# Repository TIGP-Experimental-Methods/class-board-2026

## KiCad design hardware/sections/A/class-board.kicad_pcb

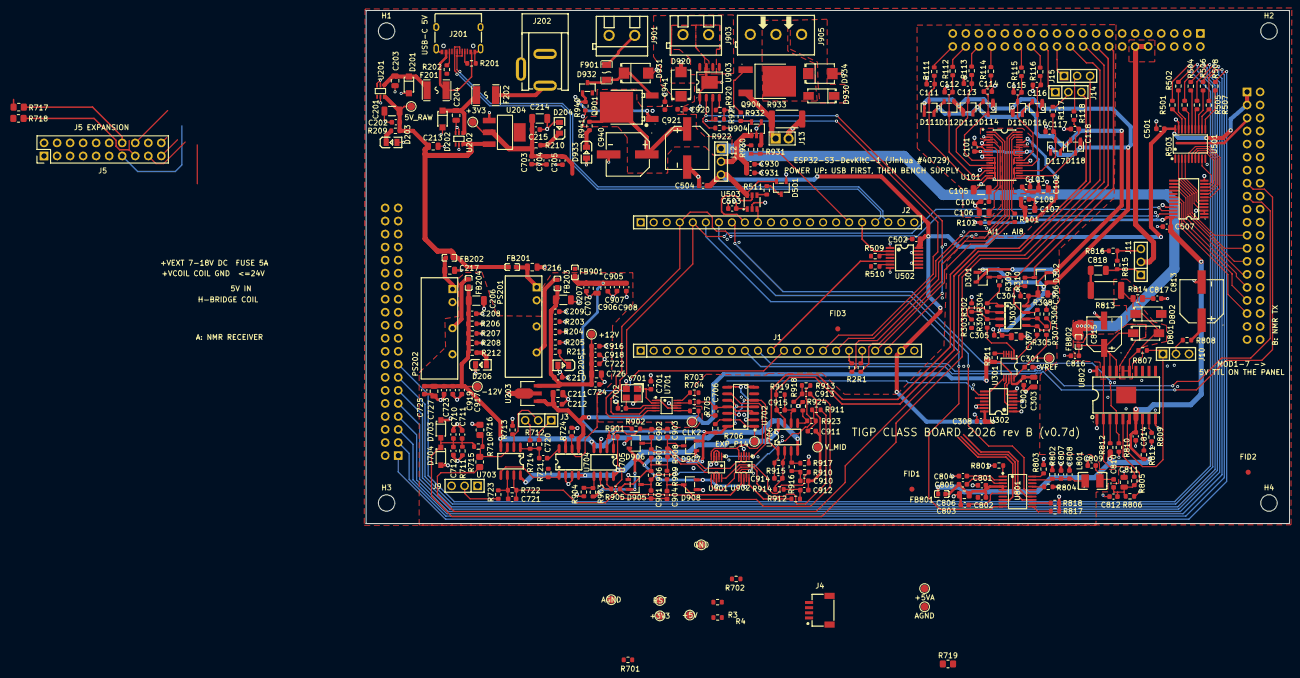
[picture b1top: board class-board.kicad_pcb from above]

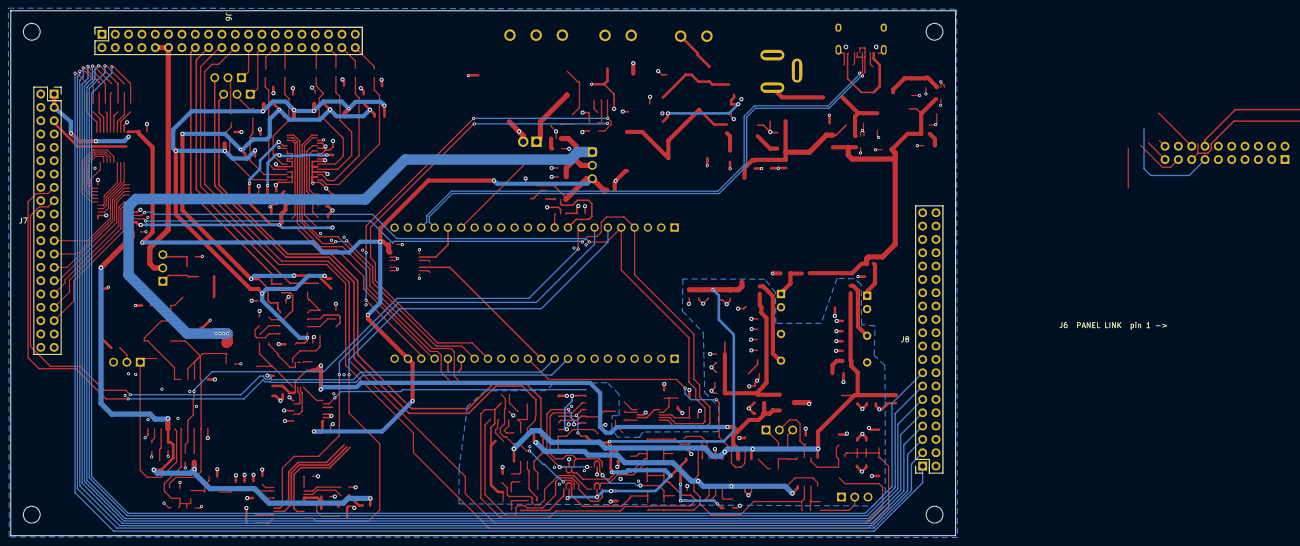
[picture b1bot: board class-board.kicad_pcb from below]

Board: 4 copper layers, 180.0 x 100.0 mm, 334 parts (3 on the bottom side), 216 nets.

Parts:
C101, C103, C104, C210, C301, C704, C810, C930: 1uF; C_0603_1608Metric
C102, C106, C107, C203, C204, C211, C213, C216, C217, C303, C306, C307, C726, C727, C806, C811, C905: 10uF; C_0805_2012Metric
C105, C201, C206, C207, C214: 22uF; C_1206_3216Metric
C108, C202, C208, C209, C212, C215, C302, C304, C305, C308, C501, C502, C503, C504, C507, C703, C705, C707, C722, C723, C724, C725, C801, C802, C803, C812, C814, C816, C906, C907, C908, C916, C917, C918, C919, C920, C931, C941: 100nF; C_0603_1608Metric
C111, C112, C113, C114, C115, C116, C117, C118: 1nF; C_0603_1608Metric
C701, C702: 3.9pF; C_0603_1608Metric
C706: 47pF; C_0603_1608Metric
C710: 1.2nF; C_0603_1608Metric
C711, C721: 100pF; C_0603_1608Metric
C712: 22pF; C_0603_1608Metric
C720, C804, C805, C817, C901, C902, C903, C904, C910, C911, C912, C913: 10nF; C_0603_1608Metric
C807: 20pF; C_0603_1608Metric
C808: 390pF; C_0603_1608Metric
C809: 130pF; C_0603_1608Metric
C813, C921, C940: 100uF 35V; CAP-SMD_BD8.0-L8.3-W8.3-LS9.3-FD
C815: 47uF 35V; CAP-SMD_BD6.3-L6.6-W6.6-FD
C818: 10uF; C_1206_3216Metric
C914, C915: 560pF; C_0603_1608Metric
D111, D112, D113, D114, D115, D116, D117, D118, D301, D302, D501, D905, D906, D907, D908: BAV99; SOT-23-3_L2.9-W1.6-P1.90-LS2.8-BR
D201, D202: SMF5.0A; SOD-123FL_L2.7-W1.8-LS3.8-RD
D203, D204, D205, D206, D933: GREEN; LED0805-R-RD
D703, D704: 1N4148W; SOD-123F_L2.7-W1.6-LS3.8-RD
D801, D802, D930: SS54; SMA_L4.4-W2.8-LS5.4-R-RD
D920, D931: SMBJ26A; SMB_L4.6-W3.6-LS5.3-RD
D932: BZX84C12; SOT-23-3_L2.9-W1.3-P1.90-LS2.4-BR
D934: SMBJ20A; SMB_L4.6-W3.6-LS5.3-RD
F201, F202: 1.5A polyfuse; F1812
F901: 5A fast; F1206
FB201, FB202, FB203, FB204, FB801, FB901: 600R@100MHz; L0603
FB802: 120R@100MHz 3A; L0603
FID1, FID2, FID3: Fiducial; Fiducial_1mm_Mask2mm
H1, H2, H3, H4: M3; MountingHole_3.2mm_M3
J1: DevKit J1 (left row); HDR-TH_22P-P2.54-V-F
J2: DevKit J3 (right row); HDR-TH_22P-P2.54-V-F
J3, J9, J10, J11, J12, J14, J15: C2937625_-_Conn_01x03; C2937625-HDR-TH_3P-P2.54-V-M
J4: Qwiic; CONN-SMD_4P-P1.00_XY-SM04B-SRSS-TB
J5: Expansion 2x10; PinHeader_2x10_P2.54mm_Vertical
J6, J7, J8: Panel link 2x20 female; PinSocket_2x20_P2.54mm_Vertical
J13: C492401-PZ254V-11-02P; C492401-HDR-TH_2P-P2.54-V-M
J201: USB-C 16P; USB-C-SMD_TYPE-C-16PIN-2MD-073
J202: DC005-T20; DC-IN-TH_DC005-T20
J901, J903: KF301-5.0-2P; CONN-TH_P5.00_KF301-5.0-2P
J905: KF301-5.0-3P; CONN-TH_3P-P5.00_KF301-5.0-3P
L801: 15uH; IND-SMD_L3.2-W2.5-LQH32CN1R0M53L
PS201, PS202: B0512S-2WR3; PWRM-TH_IBXX05S-2WR3
Q901: AOD4185; TO-252-3_L6.6-W6.1-P4.57-LS9.9-BR-CW
Q904: AOD4184A; TO-252-2_L6.6-W6.1-P4.57-LS9.9-TL-CW
R1, R2, R101, R511, R703, R705: 33; R_0603_1608Metric
R3, R4, R211, R212, R701, R702, R941: 4.7k; R_0603_1608Metric
R102, R301, R303, R305, R307, R311, R706, R721, R724, R804, R810, R811, R812, R817, R818, R903, R904, R906, R907, R908, R909, R921, R922, R930: 10k; R_0603_1608Metric
R111, R112, R113, R114, R115, R116, R117, R118, R209, R210, R501, R502, R503, R504, R505, R506, R507, R508: 1k; R_0603_1608Metric
R201, R202: 5.1k; R_0603_1608Metric
R203, R204, R205, R206, R207, R208: 2.2k; R_0603_1608Metric
R302, R304, R306, R308: 40.2k; R_0603_1608Metric
R309, R310, R509, R510: 49.9; R_0603_1608Metric
R704, R710, R713, R816, R905, R931: 100; R_0603_1608Metric
R711: 1M; R_0603_1608Metric
R712, R901, R902: 10.0k; R_0603_1608Metric
R714, R723, R910, R911, R912, R913, R914, R916, R918, R923: 1.00k; R_0603_1608Metric
R715, R716: 0R; R_0805_2012Metric_Pad1.20x1.40mm_HandSolder
R717, R718, R719: 0; R_0805_2012Metric_Pad1.20x1.40mm_HandSolder
R722: 9.1k; R_0603_1608Metric
R801: 6.8k; R_0603_1608Metric
R802, R803: 200; R_0603_1608Metric
R805, R806: 100k; R_0603_1608Metric
R807: 6.49k; R_0603_1608Metric
R808: 270; R_0603_1608Metric
R809: 11k; R_0603_1608Metric
R813: 4.7 1W; R_2512_6332Metric
R814: 10; R_0805_2012Metric
R815: 910; R_0603_1608Metric
R915, R917, R919, R924: 20.0k; R_0603_1608Metric
R920: 32k; R_0603_1608Metric
R932: 10; R_0603_1608Metric
R933: 0R; R_2512_6332Metric
R940: 47k; R_0603_1608Metric
TP1: RST; TestPoint_Pad_D1.5mm
TP2: GND; TestPoint_Pad_D1.5mm
TP3, TP202: +3V3; TestPoint_Pad_D1.5mm
TP4: +5V; TestPoint_Pad_D1.5mm
TP101, TP206: AGND; TestPoint_Pad_D1.5mm
TP201: 5V_RAW; TestPoint_Pad_D1.5mm
TP203: +12V; TestPoint_Pad_D1.5mm
TP204: -12V; TestPoint_Pad_D1.5mm
TP205: +5VA; TestPoint_Pad_D1.5mm
TP301: VREF; TestPoint_Pad_D1.5mm
TP501: EXP_P14; TestPoint_Pad_D1.5mm
TP701: CLK2; TestPoint_Pad_D1.5mm
TP702: V_MID; TestPoint_Pad_D1.5mm
U101: ADS8688IDBTR; TSSOP-38_L9.7-W4.4-P0.50-LS6.4-BL
U201, U202: LM66100DCKR; SC-70-6_L2.0-W1.3-P0.65-LS2.1-BL
U203: 78L05G-AB3-R; SOT-89-3_L4.5-W2.5-P1.50-LS4.2-BR
U204: AMS1117-3.3; SOT-223-3_L6.5-W3.4-P2.30-LS7.0-BR
U301: DAC8563SDGSR; VSSOP-10_L3.0-W3.0-P0.50-LS4.9-BL
U302, U502: 74HCT125PW; TSSOP-14_L5.0-W4.4-P0.65-LS6.4-BL
U303: OPA2192IDR; SOIC-8_L4.9-W3.9-P1.27-LS6.0-BL
U501: SN74AHCT541PWR; TSSOP-20_L6.5-W4.4-P0.65-LS6.4-BL
U503: SN74LVC1T45DBVR; SOT-23-6_L2.9-W1.6-P0.95-LS2.8-BR
U505: TCA9535PWR; TSSOP-24_L7.8-W4.4-P0.65-LS6.4-BL
U701: SI5351A-B-GT; MSOP-10_L3.0-W3.0-P0.50-LS5.0-BL
U702: 74HC74D,653; SOIC-14_L8.7-W3.9-P1.27-LS6.0-BL
U703: OPA1656IDR; SOIC-8_L5.0-W4.0-P1.27-LS6.0-BL
U704: DG419DY-T1-E3; SOIC-8_L4.9-W3.9-P1.27-LS6.0-BL
U705, U706: OPA1612AIDR; SOIC-8_L5.0-W4.0-P1.27-LS6.0-BL
U801: AD9834BRUZ; TSSOP-20_L6.5-W4.4-P0.65-LS6.4-BL
U802: OPA564AIDWPR; HSOP-20_L12.9-W7.5-P1.27-BL-EP-A
U901, U902: TS5A23157DGSR; MSOP-10_L3.0-W3.0-P0.50-LS5.0-BL
U903: DRV8871DDAR; SO-8_L4.9-W3.9-P1.27-LS6.0-BL-EP
U904: UCC27517DBVR; SOT-23-5_L3.0-W1.7-P0.95-LS2.8-BR
Y701: 25 MHz; CRYSTAL-SMD_4P-L3.2-W2.5-BL

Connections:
+3V3: C107.1, C108.1, C214.1, C215.1, C503.1, C507.1, C703.1, C704.1, C705.1, C814.1, FB801.1, FB901.1, J4.2 (3V3), J5.1, J7.5, J8.27, J8.29, R3.1, R4.1, R102.1, R210.1, R701.1, R702.1, R811.1, R812.1, TP3.1 (1_1), TP202.1 (1_1), U101.34 (DVDD), U204.2 (VOUT), U503.1 (VCCA), U505.24 (VCC), U701.1 (VDD), U701.7 (VDDO), U802.7 (VDIG)
+3V3A: C707.1, C905.1, C906.1, C907.1, C908.1, D905.2 (K2), D906.2 (K2), D907.2 (K2), D908.2 (K2), FB901.2, R706.1, R903.1, U702.4 (~1PRE), U702.10 (~2PRE), U702.14 (VCC), U901.8 (V+), U902.8 (V+)
+5VA: C101.1, C102.1, C103.1, C211.1, C212.1, C302.1, C303.1, R311.2, TP205.1 (1_1), U101.9 (AVDD), U101.30 (AVDD), U203.1 (OUT), U301.9 (AVDD), U704.5 (VL)
+5V_RAW: C201.1, C202.1, C213.1, C308.1, C501.1, C502.1, C504.1, D501.2 (K2), FB201.1, FB202.1, J1.21 (5V), J5.2, J7.1, J7.3, J12.3, R209.1, TP4.1 (1_1), TP201.1 (1_1), U201.6 (VOUT), U202.6 (VOUT), U204.3 (VIN), U302.14 (VCC), U501.20 (VCC), U502.14 (VCC), U503.6 (VCCB)
+12V: C207.1, C209.1, C210.1, C304.1, C306.1, C722.1, C724.1, C726.1, C916.1, C918.1, D111.2 (K2), D112.2 (K2), D113.2 (K2), D114.2 (K2), D115.2 (K2), D116.2 (K2), D117.2 (K2), D118.2 (K2), D301.2 (K2), D302.2 (K2), FB203.2, J5.3, R203.1, R204.1, R205.1, R211.1, TP203.1 (1_1), U203.3 (IN), U303.8 (V+), U703.8 (V+), U704.4 (V+), U705.8 (V+), U706.8 (V+)
+VCOIL: D930.2 (K), J905.1
+VEXT: C920.1, C921.1, C940.1, C941.1, D920.1 (K), FB802.1, J12.1, Q901.2 (D), R941.1, U903.5 (VM)
-12V: C206.1, C208.1, C305.1, C307.1, C723.1, C725.1, C727.1, C917.1, C919.1, D111.1 (A1), D112.1 (A1), D113.1 (A1), D114.1 (A1), D115.1 (A1), D116.1 (A1), D117.1 (A1), D118.1 (A1), D301.1 (A1), D302.1 (A1), FB204.2, J5.4, R206.1, R207.1, R208.1, R212.1, TP204.1 (1_1), U303.4 (V-), U703.4 (V-), U704.7 (V-), U705.4 (V-), U706.4 (V-)
/b1_inputs/ADC_RST: R102.2, U101.2 (~RST/~PD)
/b1_inputs/AI1: J6.40, R111.1
/b1_inputs/AI2: J6.38, R112.1
/b1_inputs/AI3: J6.36, R113.1
/b1_inputs/AI4: J6.34, R114.1
/b1_inputs/AI5: J6.30, R115.1
/b1_inputs/AI6: J6.28, R116.1
/b1_inputs/AI7: J6.26, J14.1
/b1_inputs/AI8: J6.24, J15.1
/b1_inputs/AIN1: C111.1, D111.3 (COM), R111.2, U101.18 (AIN_1P)
/b1_inputs/AIN2: C112.1, D112.3 (COM), R112.2, U101.16 (AIN_0P)
/b1_inputs/AIN3: C113.1, D113.3 (COM), R113.2, U101.14 (AIN_7P)
/b1_inputs/AIN4: C114.1, D114.3 (COM), R114.2, U101.12 (AIN_6P)
/b1_inputs/AIN5: C115.1, D115.3 (COM), R115.2, U101.27 (AIN_5P)
/b1_inputs/AIN6: C116.1, D116.3 (COM), R116.2, U101.25 (AIN_4P)
/b1_inputs/AIN7: C117.1, D117.3 (COM), R117.2, U101.23 (AIN_3P)
/b1_inputs/AIN8: C118.1, D118.3 (COM), R118.2, U101.21 (AIN_2P)
/b1_inputs/AO1: D301.3 (COM), J6.18, R309.2
/b1_inputs/AO2: D302.3 (COM), J6.16, R310.2
/b1_inputs/AUX: C710.2, C711.2, C712.2, D703.2 (A), D704.1 (K), J6.20, R710.2, R711.2
/b1_inputs/COND_OUT1: C914.2, J14.3, R915.2, U706.1
/b1_inputs/COND_OUT2: C915.2, J15.3, R919.2, U706.7
/b1_inputs/CS_ADC: J1.16 (IO10), U101.38 (~CS)
/b1_inputs/RX: J6.22, R715.2
/b1_inputs/TX: J6.10, J6.12, J11.2
/b2_power/USB_D_N: J2.20 (IO19), J201.A7 (D-), J201.B7 (D-)
/b2_power/USB_D_P: J2.19 (IO20), J201.A6 (D+), J201.B6 (D+)
/b3_outputs/CS_DAC: J1.5 (IO5), U302.9 (3A)
/b3_outputs/DAC_A: R301.1, U301.1 (VOUTA)
/b3_outputs/DAC_B: R305.1, U301.2 (VOUTB)
/b3_outputs/DAC_DIN: U301.8 (DIN), U302.6 (2Y)
/b3_outputs/DAC_SCLK: U301.7 (SCLK), U302.3 (1Y)
/b3_outputs/DAC_SYNC: U301.6 (~SYNC), U302.8 (3Y)
/b3_outputs/VREF_DAC: C301.1, R303.1, R307.1, TP301.1 (1_1), U301.10 (VREFIN/VREFOUT)
/b5_dio_trig/DIO1: U501.2 (A1), U505.4 (P00)
/b5_dio_trig/DIO2: U501.3 (A2), U505.5 (P01)
/b5_dio_trig/DIO3: U501.4 (A3), U505.6 (P02)
/b5_dio_trig/DIO4: U501.5 (A4), U505.7 (P03)
/b5_dio_trig/DIO5: U501.6 (A5), U505.8 (P04)
/b5_dio_trig/DIO6: U501.7 (A6), U505.9 (P05)
/b5_dio_trig/DIO7: U501.8 (A7), U505.10 (P06)
/b5_dio_trig/DIO8: U501.9 (A8), U505.11 (P07)
/b5_dio_trig/EXP_P14: R706.2, TP501.1 (1_1), U505.17 (P14), U702.1 (~1CLR), U702.13 (~2CLR)
/b5_dio_trig/FASTTTL1: J8.39, R509.2
/b5_dio_trig/FASTTTL2: J8.37, R510.2
/b5_dio_trig/FAST_OUT1: J2.18 (IO21), U502.2 (1A)
/b5_dio_trig/FAST_OUT2: J1.11 (IO18), U502.5 (2A)
/b5_dio_trig/LED_ACT: J8.23, R718.2
/b5_dio_trig/LED_WIFI: J8.25, R717.2
/b5_dio_trig/MOD1: J7.23, U505.13 (P10)
/b5_dio_trig/MOD2: J7.25, U505.14 (P11)
/b5_dio_trig/MOD3: J7.27, U505.15 (P12)
/b5_dio_trig/MOD4: J7.29, U505.16 (P13)
/b5_dio_trig/MOD5: J7.31, U505.18 (P15)
/b5_dio_trig/MOD6: J7.33, U505.19 (P16)
/b5_dio_trig/MOD7: J7.35, U505.20 (P17)
/b5_dio_trig/OPTO_IN1: J1.9 (IO16), J7.15
/b5_dio_trig/OPTO_IN2: J1.10 (IO17), J7.17
/b5_dio_trig/TRIG_5V: D501.3 (COM), J8.35, R511.2
/b5_dio_trig/TRIG_DIR: J2.9 (IO39), U503.5 (DIR)
/b5_dio_trig/TTL1: J8.15, R501.2
/b5_dio_trig/TTL2: J8.13, R502.2
/b5_dio_trig/TTL3: J8.11, R503.2
/b5_dio_trig/TTL4: J8.9, R504.2
/b5_dio_trig/TTL5: J8.7, R505.2
/b5_dio_trig/TTL6: J8.5, R506.2
/b5_dio_trig/TTL7: J8.3, R507.2
/b5_dio_trig/TTL8: J8.1, R508.2
/base_mcu/DDS_FSYNC: J2.7 (IO41), U801.15 (~FSYNC)
/base_mcu/DDS_PSEL: J2.6 (IO42), U801.10 (PSELECT)
/base_mcu/FET_GATE: J2.17 (IO47), R930.1, R931.1
/base_mcu/GPIO4: J1.4 (IO4), J5.16
/base_mcu/GPIO6: J1.6 (IO6), J5.17
/base_mcu/GPIO7: J1.7 (IO7), J5.19
/base_mcu/GPIO15: J1.8 (IO15), J5.20
/base_mcu/GPIO43: J2.2 (IO43/TX), J5.14, R717.1
/base_mcu/GPIO44: J2.3 (IO44/RX), J5.15, R718.1
/base_mcu/HB_IN1: J1.15 (IO9), R921.1, U903.3 (IN1)
/base_mcu/HB_IN2: J1.20 (IO14), R922.1, U903.2 (IN2)
/base_mcu/MOSI_MCU: J1.17 (IO11), R2.1
/base_mcu/RST: J1.3 (RST), TP1.1 (1_1)
/base_mcu/RX_BLANK: J1.12 (IO8), R724.1, U704.6 (IN)
/base_mcu/SCLK_MCU: J1.18 (IO12), R1.1
/base_mcu/TRIG_IO: J2.10 (IO38), J5.13, U503.3 (A)
/base_mcu/TX_EN: J2.8 (IO40), R810.1, U802.4 (E/~S)
/c_switch/COIL: D930.1 (A), D934.1 (K), J905.2, Q904.2 (D)
/c_switch/HB_OUT1: J903.1, U903.6 (OUT1)
/c_switch/HB_OUT2: J903.2, U903.8 (OUT2)
/c_switch/ILIM: R920.1, U903.4 (ILIM)
/c_switch/ISENSE_COIL: J13.1, Q904.3 (S), R933.1
/c_switch/VDD904: C930.1, C931.1, J12.2, U904.1 (VDD)
/c_switch/VIN: F901.1, J901.1
/c_switch/VIN_F: D931.1 (K), D932.3 (K), F901.2, Q901.3 (S)
/nmr_rx/BLK_IN: C720.2, U704.8 (S2)
/nmr_rx/CLK0_MCLK: R703.2, U801.8 (MCLK)
/nmr_rx/CLK1: C706.1, R704.2, U702.3 (1CLK), U702.11 (2CLK)
/nmr_rx/DIF_I_N: C914.1, R914.2, R915.1, U706.2 (-)
/nmr_rx/DIF_I_P: R916.2, R917.1, U706.3 (+)
/nmr_rx/DIF_Q_N: C915.1, R918.2, R919.1, U706.6 (-)
/nmr_rx/DIF_Q_P: R923.1, R924.1, U706.5 (+)
/nmr_rx/IF_IN: R912.1, U902.10 (COM1)
/nmr_rx/IF_INF: C912.1, R912.2, R914.1
/nmr_rx/IF_IP: R910.1, U901.10 (COM1)
/nmr_rx/IF_IPF: C910.2, R910.2, R916.1
/nmr_rx/IF_QN: R913.1, U902.6 (COM2)
/nmr_rx/IF_QNF: C913.1, R913.2, R918.1
/nmr_rx/IF_QP: R911.1, U901.6 (COM2)
/nmr_rx/IF_QPF: C911.2, R911.2, R923.2
/nmr_rx/INV_N: R901.2, R902.1, U705.2 (-)
/nmr_rx/LNA1_OUT: C720.1, R712.1, R714.1, U703.1
/nmr_rx/LNA_FB1: J3.2, R713.1, U703.2 (-)
/nmr_rx/LNA_FB2: C721.1, R722.1, R723.1, U703.6 (-)
/nmr_rx/LNA_OUT: C721.2, C901.1, C904.1, R722.2, R901.1, U703.7
/nmr_rx/LO_I: U702.5 (1Q), U702.12 (2D), U901.1 (IN1), U902.1 (IN1)
/nmr_rx/LO_Q: U702.9 (2Q), U901.5 (IN2), U902.5 (IN2)
/nmr_rx/LO_QN: U702.2 (1D), U702.8 (~2Q)
/nmr_rx/RX_IN: R710.1, R715.1, R716.2, U703.3 (+)
/nmr_rx/SN_A: C902.2, D906.3 (COM), R907.1, U901.7 (NC2), U901.9 (NC1)
/nmr_rx/SN_B: C903.2, D907.3 (COM), R908.1, U902.2 (NO1), U902.4 (NO2)
/nmr_rx/SP_A: C901.2, D905.3 (COM), R906.1, U901.2 (NO1), U901.4 (NO2)
/nmr_rx/SP_B: C904.2, D908.3 (COM), R909.1, U902.7 (NC2), U902.9 (NC1)
/nmr_rx/ST2_GAIN: J9.2, R723.2
/nmr_rx/ST2_IN: R721.1, U703.5 (+), U704.1 (D)
/nmr_rx/S_MINUS: C902.1, C903.1, R902.2, U705.1
/nmr_rx/VMID_BUF: R905.1, U705.6 (-), U705.7
/nmr_rx/VMID_DIV: R903.2, R904.1, U705.5 (+)
/nmr_rx/XTAL_A: C701.1, U701.2 (XA), Y701.1 (OSC1)
/nmr_rx/XTAL_B: C702.1, U701.3 (XB), Y701.3 (OSC2)
/nmr_tx/+3V3D: C801.1, C802.1, C805.2, C806.1, FB801.2, U801.4 (AVDD), U801.5 (DVDD)
/nmr_tx/+VEXT_TX: C815.1, C816.1, D801.2 (K), FB802.2, R805.1, U802.2 (V+), U802.17 (V+PWR), U802.18 (V+PWR), U802.19 (V+PWR)
/nmr_tx/DDS_RESET: R817.1, U801.11 (RESET)
/nmr_tx/DDS_SLEEP: R818.1, U801.12 (SLEEP)
/nmr_tx/TX_A: D801.1 (A), D802.2 (K), R807.2, R813.1, R814.1, U802.15 (VOUT), U802.16 (VOUT)
/nmr_tx/TX_FB: J10.1, R807.1, U802.6 (-IN)
/nmr_tx/TX_IFLAG: R811.2, U802.8 (IFLAG)
/nmr_tx/TX_TFLAG: R812.2, U802.3 (TFLAG)
/nmr_tx/TX_VMID: C810.2, C811.1, C812.1, R805.2, R806.1, U802.5 (+IN)
AGND: C101.2, C102.2, C103.2, C104.2, C105.2, C106.2, C111.2, C112.2, C113.2, C114.2, C115.2, C116.2, C117.2, C118.2, C206.2, C207.2, C208.2, C209.2, C210.2, C211.2, C212.2, C301.2, C302.2, C303.2, C304.2, C305.2, C306.2, C307.2, C706.2, C707.2, C710.1, C711.1, C712.1, C722.2, C723.2, C724.2, C725.2, C726.2, C727.2, C801.2, C802.2, C803.2, C804.2, C806.2, C807.2, C808.2, C809.2, C905.2, C906.2, C907.2, C908.2, C916.2, C917.2, C918.2, C919.2, D205.1 (K), D206.2 (A), D703.1 (K), D704.2 (A), D905.1 (A1), D906.1 (A1), D907.1 (A1), D908.1 (A1), J5.18, J6.15, J6.17, J6.19, J6.21, J6.23, J6.25, J6.27, J6.29, J6.31, J6.33, J6.35, J6.37, J6.39, J9.1, PS201.4 (-VO), PS202.6 (+VO), R203.2, R204.2, R205.2, R206.2, R207.2, R208.2, R302.1, R306.1, R711.1, R713.2, R716.1, R719.1, R721.2, R724.2, R801.2, R802.2, R803.2, R804.2, R817.2, R818.2, R904.2, R917.2, R924.2, TP101.1 (1_1), TP206.1 (1_1), U101.4 (~REFSEL), U101.6 (REFGND), U101.8 (AGND), U101.10 (AUX_IN), U101.11 (AUX_GND), U101.13 (AIN_6GND), U101.15 (AIN_7GND), U101.17 (AIN_0GND), U101.19 (AIN_1GND), U101.20 (AIN_2GND), U101.22 (AIN_3GND), U101.24 (AIN_4GND), U101.26 (AIN_5GND), U101.28 (AGND), U101.29 (AGND), U101.31 (AGND), U101.32 (AGND), U203.2 (GND), U301.3 (GND), U301.4 (~LDAC), U702.7 (GND), U704.2 (S1), U704.3 (GND), U705.3 (+), U801.7 (DGND), U801.9 (FSELECT), U801.18 (AGND), U901.3 (GND), U902.3 (GND)
GND: C107.2, C108.2, C201.2, C202.2, C203.2, C204.2, C213.2, C214.2, C215.2, C216.2, C217.2, C308.2, C501.2, C502.2, C503.2, C504.2, C507.2, C701.2, C702.2, C703.2, C704.2, C705.2, C811.2, C812.2, C813.2, C814.2, C815.2, C816.2, C817.2, C920.2, C921.2, C930.2, C931.2, C940.2, C941.2, D201.2 (A), D202.2 (A), D203.1 (K), D204.1 (K), D501.1 (A1), D802.1 (A), D920.2 (A), D931.2 (A), D933.1 (K), D934.2 (A), J1.22 (GND), J2.1 (GND), J2.21 (GND), J2.22 (GND), J4.1 (GND), J4.5 (SHELL), J4.6 (SHELL), J5.5, J5.6, J5.10, J6.1, J6.3, J6.5, J6.7, J6.9, J6.11, J7.2, J7.4, J7.6, J7.8, J7.10, J7.12, J7.14, J7.16, J7.18, J7.20, J7.22, J7.24, J7.26, J7.28, J7.30, J7.32, J7.34, J7.36, J7.38, J7.40, J8.2, J8.4, J8.6, J8.8, J8.10, J8.12, J8.14, J8.16, J8.18, J8.20, J8.22, J8.24, J8.26, J8.28, J8.30, J8.32, J8.34, J8.36, J8.38, J8.40, J13.2, J201.13 (SHIELD), J201.14 (SHIELD), J201.A1B12 (GND), J201.B1A12 (GND), J202.2 (SLEEVE), J901.2, J905.3, PS201.2 (-VIN), PS202.2 (-VIN), R201.2, R202.2, R719.2, R806.2, R809.2, R810.2, R816.2, R920.2, R921.2, R922.2, R930.2, R933.2, R940.2, TP2.1 (1_1), U101.3 (DAISY), U101.33 (DGND), U201.2 (GND), U201.3 (~CE), U201.5 (~ST), U202.2 (GND), U202.3 (~CE), U202.5 (~ST), U204.1 (GND), U302.1 (~1OE), U302.4 (~2OE), U302.7 (GND), U302.10 (~3OE), U302.12 (4A), U302.13 (~4OE), U501.1 (~OE1), U501.10 (GND), U501.19 (~OE2), U502.1 (~1OE), U502.4 (~2OE), U502.7 (GND), U502.9 (3A), U502.10 (~3OE), U502.12 (4A), U502.13 (~4OE), U503.2 (GND), U505.2 (A1), U505.3 (A2), U505.12 (GND), U505.21 (A0), U701.8 (GND), U802.1 (V-), U802.10 (V-), U802.11 (V-), U802.13 (V-PWR), U802.14 (V-PWR), U802.20 (V-), U802.21 (EP), U903.1 (GND), U903.7 (PGND), U903.9 (EP), U904.2 (GND), U904.4 (IN-), Y701.2 (GND), Y701.4 (GND)
I2C_SCL: J2.5 (IO2), J4.4 (SCL), J5.12, J8.31, R4.2, R702.2, U505.22 (SCL), U701.4 (SCL)
I2C_SDA: J2.4 (IO1), J4.3 (SDA), J5.11, J8.33, R3.2, R701.2, U505.23 (SDA), U701.5 (SDA)
unnamed: C809.1, C810.1, L801.2
unnamed: C813.1, R808.2
unnamed: C817.1, R814.2
unnamed: C818.1, R813.2
unnamed: C203.1, D201.1 (K), F201.2, U201.1 (VIN)
unnamed: C204.1, D202.1 (K), F202.2, U202.1 (VIN)
unnamed: D203.2 (A), R209.2
unnamed: D204.2 (A), R210.2
unnamed: D205.2 (A), R211.2
unnamed: D206.1 (K), R212.2
unnamed: D932.1 (A), Q901.1 (G), R940.1
unnamed: D933.2 (A), R941.2
unnamed: F201.1, J201.A4B9 (VBUS), J201.B4A9 (VBUS)
unnamed: J3.1, R712.2
unnamed: J3.3, R714.2
unnamed: J10.2, R808.1
unnamed: C818.2, J11.1, R815.1
unnamed: J11.3, R815.2, R816.1
unnamed: J14.2, R117.1
unnamed: J15.2, R118.1
unnamed: J201.A5 (CC1), R201.1
unnamed: J201.B5 (CC2), R202.1
unnamed: F202.1, J202.1 (TIP)
unnamed: C216.1, FB201.2, PS201.1 (+VIN)
unnamed: FB203.1, PS201.6 (+VO)
unnamed: C217.1, FB202.2, PS202.1 (+VIN)
unnamed: FB204.1, PS202.4 (-VO)
unnamed: Q904.1 (G), R932.2
unnamed: R304.2, R309.1, U303.1
unnamed: R308.2, R310.1, U303.7
unnamed: R705.2, TP701.1 (1_1)
unnamed: C104.1, C105.1, U101.7 (REFCAP)
unnamed: C106.1, U101.5 (REFIO)
unnamed: R101.1, U101.36 (SDO)
unnamed: R311.1, U301.5 (~CLR)
unnamed: R301.2, R302.2, U303.3 (+)
unnamed: R303.2, R304.1, U303.2 (-)
unnamed: R305.2, R306.2, U303.5 (+)
unnamed: R307.2, R308.1, U303.6 (-)
unnamed: R501.1, U501.18 (Y1)
unnamed: R502.1, U501.17 (Y2)
unnamed: R503.1, U501.16 (Y3)
unnamed: R504.1, U501.15 (Y4)
unnamed: R505.1, U501.14 (Y5)
unnamed: R506.1, U501.13 (Y6)
unnamed: R507.1, U501.12 (Y7)
unnamed: R508.1, U501.11 (Y8)
unnamed: R509.1, U502.3 (1Y)
unnamed: R510.1, U502.6 (2Y)
unnamed: R511.1, U503.4 (B)
unnamed: R703.1, U701.10 (CLK0)
unnamed: R704.1, U701.9 (CLK1)
unnamed: R705.1, U701.6 (CLK2)
unnamed: C803.1, U801.6 (CAP/2.5V)
unnamed: C805.1, U801.3 (COMP)
unnamed: R801.1, U801.1 (FS_ADJUST)
unnamed: C807.1, C808.1, L801.1, R802.1, U801.19 (IOUT)
unnamed: R803.1, U801.20 (IOUTB)
unnamed: C804.1, U801.2 (REFOUT)
unnamed: R804.1, U801.17 (VIN)
unnamed: R809.1, U802.9 (ISET)
unnamed: R931.2, U904.3 (IN+)
unnamed: R932.1, U904.5 (OUT)
SPI_MISO: J1.19 (IO13), J5.9, R101.2
SPI_MOSI: J5.8, R2.2, U101.1 (SDI), U302.5 (2A), U801.13 (SDATA)
SPI_SCLK: J5.7, R1.2, U101.37 (SCLK), U302.2 (1A), U801.14 (SCLK)
V_MID: C910.1, C911.1, C912.2, C913.2, R905.2, R906.2, R907.2, R908.2, R909.2, TP702.1 (1_1)
